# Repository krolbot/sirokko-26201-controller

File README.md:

# Sirokko 262.01

Контроллер отопителя Sirokko 262.01 на ESP32-S3. Управляет розжигом, муфтой топливного насоса и вентилятором, поддерживает температуру помещения. Управление — с TFT-панели с энкодером или из браузера по Wi-Fi.

[Скачать прошивку](https://github.com/krolbot/sirokko-26201-controller/releases/latest/download/Sirokko-firmware.zip) · [Руководство пользователя](docs/user-guide.md) · [Схема PDF](hardware/schematic.pdf)

## Возможности

- Розжиг, контроль температур и охлаждающая продувка после остановки.
- Ручное управление и поддержание температуры помещения, таймер отключения.
- Две термопары K через MAX31856 и комнатный датчик DS18B20.
- TFT 2,4″ с энкодером EC11 и кнопкой пуска/остановки; веб-интерфейс на русском языке.
- Подписанные обновления прошивки по Wi-Fi.

Питание — **24 В DC**. Вентилятор подключается через внешний регулятор **HC-160A S2**. Используется модуль **YD-ESP32-S3 N16R8 V1.4**.

Проект не испытывался на реальном оборудовании.

## Плата и компоненты

[Ведомость компонентов](hardware/BOM.md) содержит артикулы, количества, ссылки ChipDip и требования к внешним модулям. Есть [CSV](hardware/bom.csv) для закупки. Подключения, распиновки и порядок монтажа — в [инструкции сборки](docs/assembly.md).

Для заказа голой платы нужен [Gerber ZIP](manufacturing/pcb/gerbers.zip): **281 × 170 мм, 2 слоя, FR-4 1,6 мм, медь 35 мкм**. Для заказа монтажа — [BOM, координаты и сборочный чертёж](manufacturing/README.md).

## Прошивка

[Готовый USB-комплект](https://github.com/krolbot/sirokko-26201-controller/releases/latest/download/Sirokko-firmware.zip) включает загрузчик, таблицу разделов и приложение. [Руководство](docs/user-guide.md) описывает запись, первоначальную настройку и управление. Перед первым запуском задайте параметры отопителя по руководству.

Для сборки из исходников нужны ESP-IDF **5.2.3** и Node.js **26**. Команды сборки и подписи OTA — в [firmware/README.md](firmware/README.md).

## Файлы проекта

- [hardware/](hardware/) — проект KiCad 10, библиотеки, схема и компоненты.
- [firmware/](firmware/) — прошивка ESP32-S3 и веб-интерфейс.
- [manufacturing/](manufacturing/) — Gerber, сверловка, BOM и координаты для монтажа.
- [docs/](docs/) — сборка, подключение и руководство пользователя.

[Все файлы выпуска](https://github.com/krolbot/sirokko-26201-controller/releases/latest) · [Сообщить о проблеме](https://github.com/krolbot/sirokko-26201-controller/issues)

## Лицензии

Общая лицензия не назначена. Лицензии сторонних материалов: [KiCad](hardware/KICAD_LIBRARIES_LICENSE.md), [прошивка](firmware/third_party/README.md), [веб-интерфейс](firmware/web_ui/THIRD_PARTY_NOTICES.txt).

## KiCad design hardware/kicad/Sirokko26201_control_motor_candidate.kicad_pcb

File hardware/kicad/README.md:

> **Статус этапов:** проект платы, разводка и комплект изготовления завершены и приняты. Изготовление/сборка, реализация прошивки и физические испытания — следующие отдельные этапы. Отсутствие испытаний или готовой прошивки само по себе не блокирует изготовление голой PCB. Следующий совместный шаг — согласование функционала прошивки без изменения кода. [Подробнее / Stage definitions](../../docs/PROJECT_STAGES_RU.md).

# KiCad — действующий проект Sirokko

Открывайте `Sirokko26201_control_motor_candidate.kicad_pro` в KiCad 10.0.8. В комплекте одна основная PCB, пять листов схемы, библиотеки и проектные модели. Вместо собственной панели используется покупной TFT 2.4″ + EC11.

- PCB SHA256: `0ed3728e0cd427c01e9509a6aff25a2870087f775708396bfdd9fabb0b346e82`.
- Root SCH SHA256: `0b85bf2f4921b25a1c3126348eb176a88c7e3b29ca474c2d7229c4367e0a5cf5`.
- PRO SHA256: `11029d86464484cea63d73aa802bad95c1a6805aee11e841fc78322e9d2bc0d6`.
- Контур 281 × 170 мм; 73 посадки, 303 площадки, 663 сегмента, 115 переходов, 25 зон.
- DRC: 0 нарушений, 0 разрывов, без ignored checks. ERC: 0 зарегистрированных нарушений при четырёх сохранённых проектных ignored checks.
- Сверены 252 электрических назначения pin→net, 251 отверстие и 60 позиций установки. Сохранены UUID, сети и локальная геометрия всех 303 площадок; В v6 J32 и правый блок перекомпонованы; в v7 переразведены цепи и перенесены R7/R8 для свободного доступа к J29. 178 → 147 → 115 переходов; глобальный минимум не доказан.

**Окончательные управляющие выводы TFT:** RES = GPIO6/J1.6; DC = GPIO41/J3.7; CS = GPIO42/J3.6. Загрузочные GPIO3/46 не используются. GPIO9/10 остаются выборами MAX31856 и не заняты TFT. Старые описания назначения DC/CS на GPIO9/10 неверны.

J32 — IDC 2×6, SPI 3.3 В, кабель до 100 мм. Соединение с модулем не 1:1: [точная распиновка](../../docs/TFT24_INTERFACE_RU.md). [Текущие файлы изготовления и проверки](../../manufacturing/current/README_RU.md).

Неиспользуемые библиотечные символы не являются установленными компонентами. Стандартные и условные 3D-модели не доказывают полную геометрию сборки. `production_release=false`, `physical_tests=false`; KEY0 подключена аппаратно. Её программный обработчик не входит в этот выпуск; прошивка и локальный интерфейс требуют согласования.

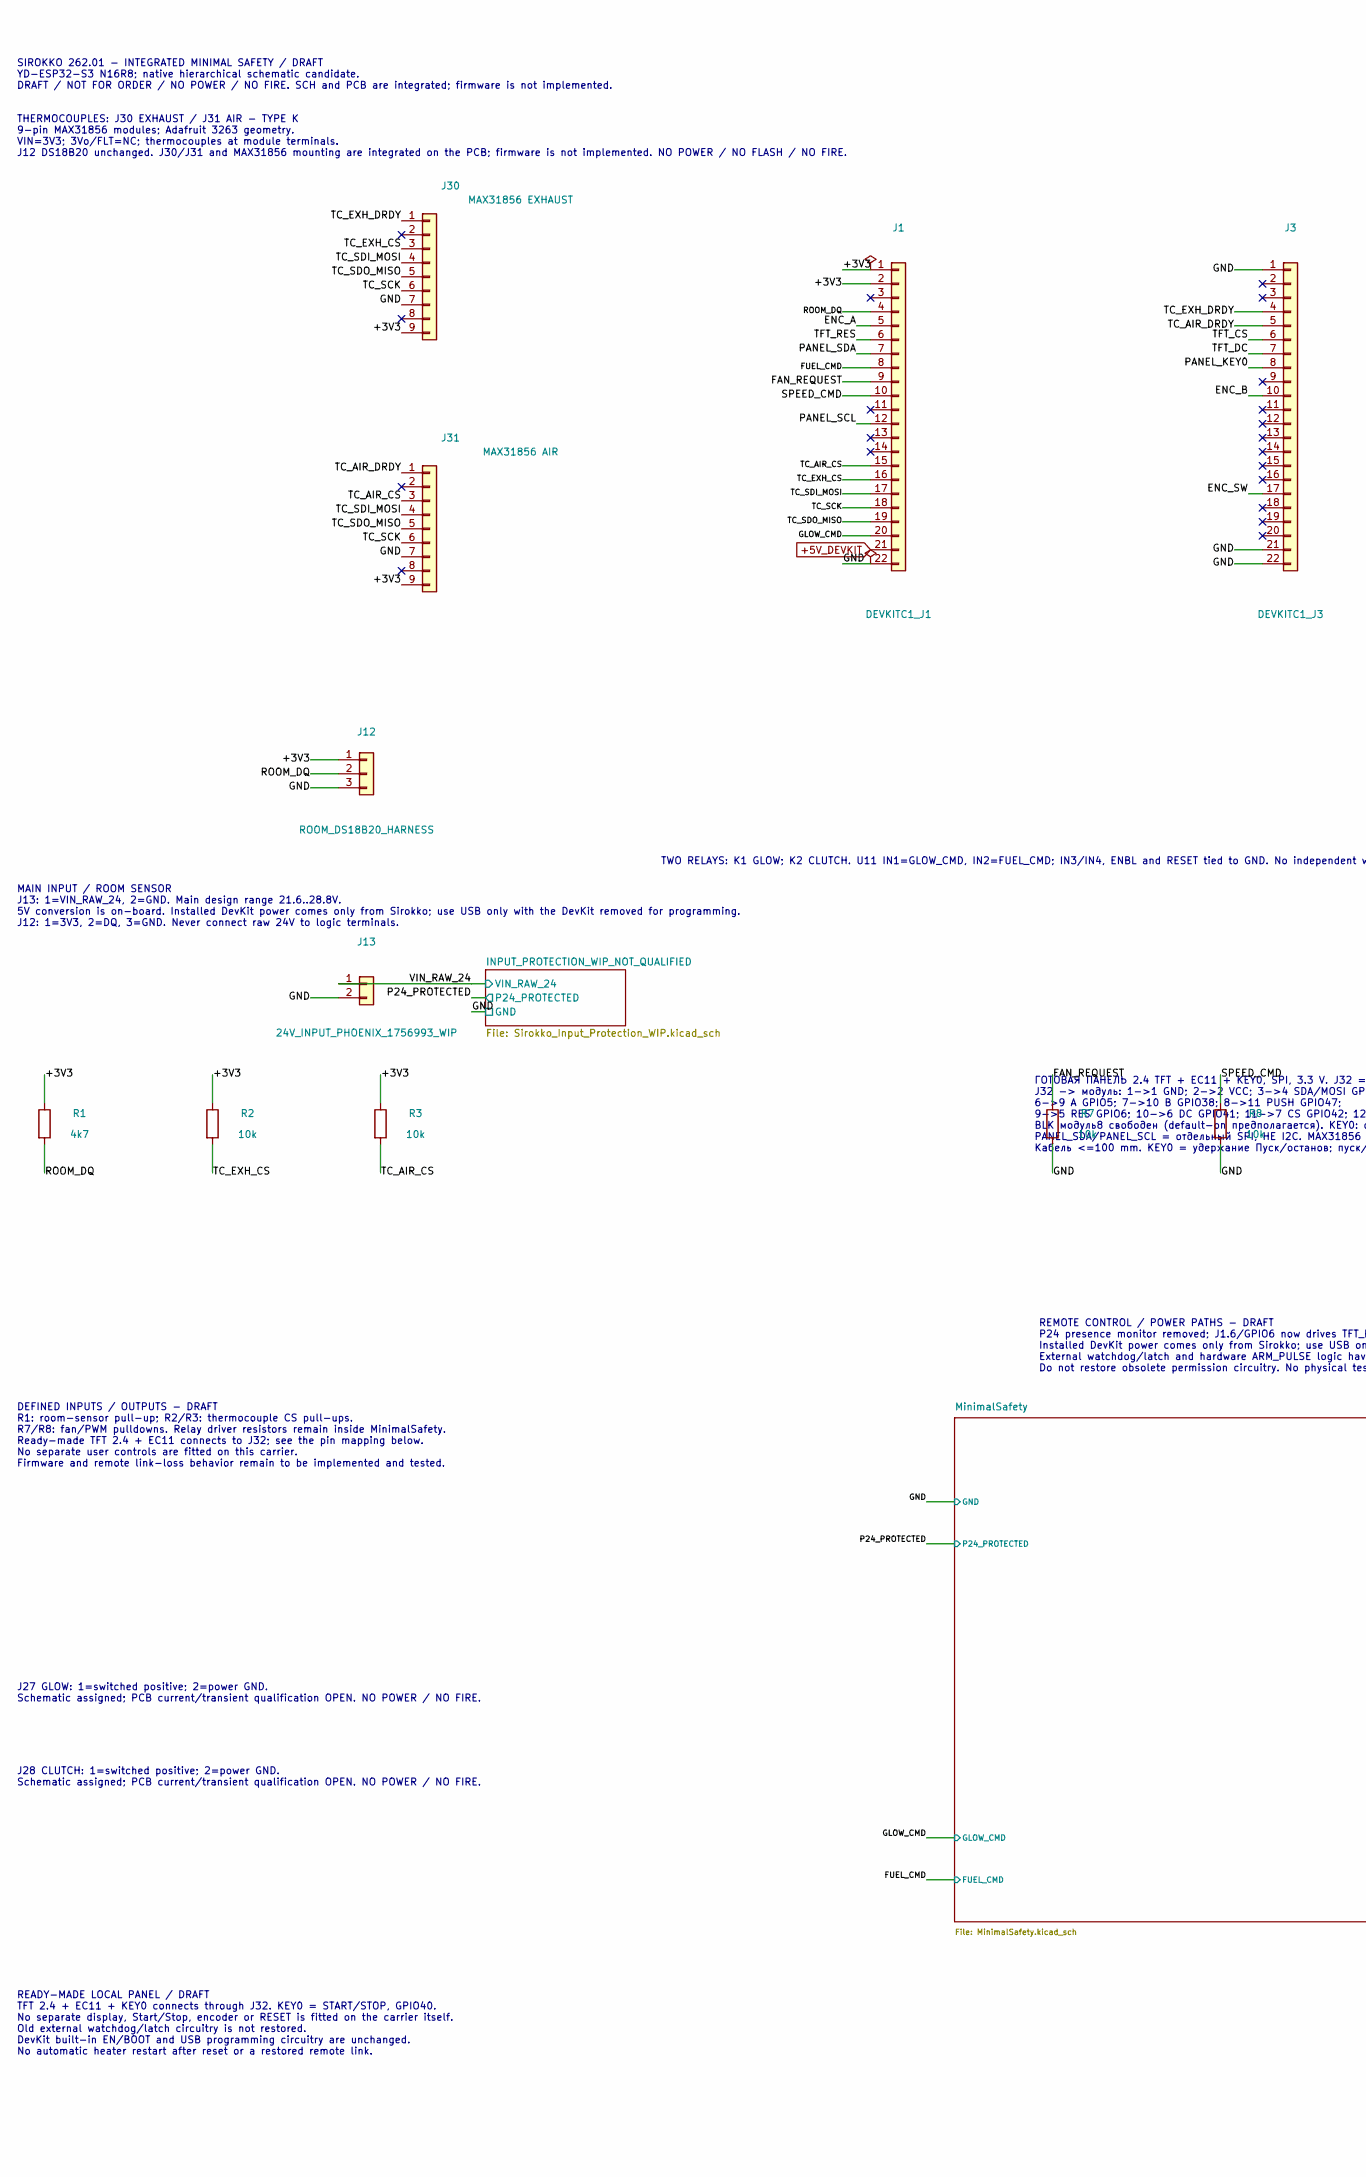
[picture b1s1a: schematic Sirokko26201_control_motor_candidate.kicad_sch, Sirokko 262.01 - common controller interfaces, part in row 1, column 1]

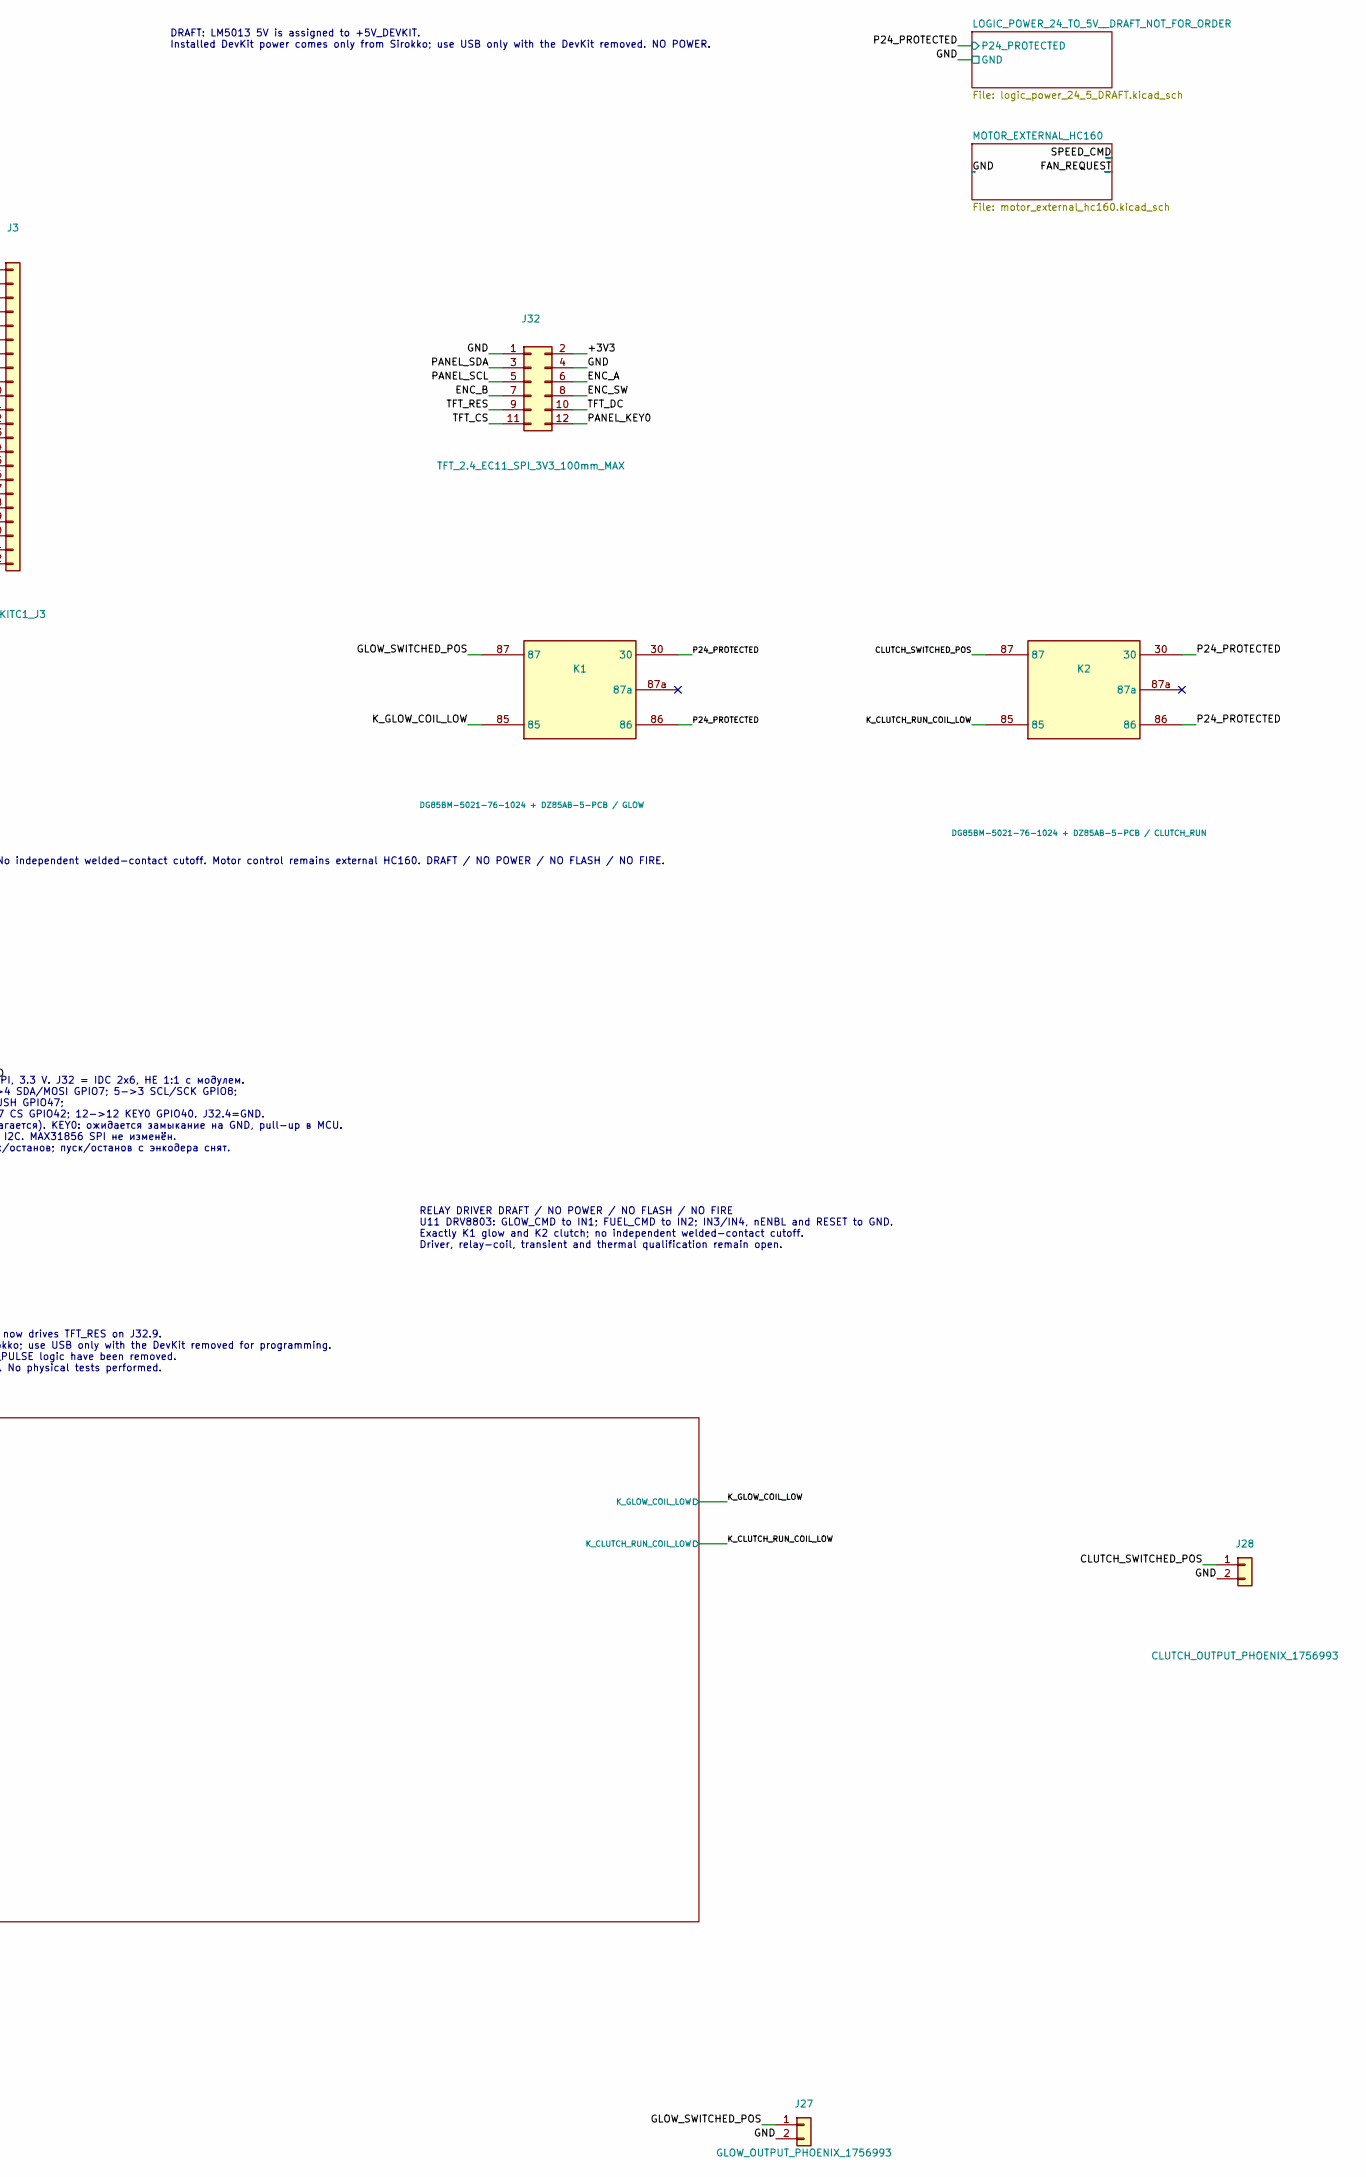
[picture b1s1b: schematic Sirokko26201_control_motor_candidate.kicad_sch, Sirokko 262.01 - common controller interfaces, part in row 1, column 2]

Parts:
J1: DEVKITC1_J1; PinSocket_1x22_P2.54mm_Vertical; MPN SSQ-122-01-T-S
J3: DEVKITC1_J3; PinSocket_1x22_P2.54mm_Vertical; MPN SSQ-122-01-T-S
J12: ROOM_DS18B20_HARNESS; TerminalBlock_Phoenix_MKDS-1,5-3-5.08_1x03_P5.08mm_Horizont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; MPN 1715734
J13: 24V_INPUT_PHOENIX_1756993_WIP; Phoenix_1756993_MKDS5HV_2_9.52_ZSZS_3D_ENVELOPE; MPN 1756993
J27: GLOW_OUTPUT_PHOENIX_1756993; Phoenix_1756993_MKDS5HV_2_9.52_ZSZS_3D_ENVELOPE; MPN 1756993
J28: CLUTCH_OUTPUT_PHOENIX_1756993; Phoenix_1756993_MKDS5HV_2_9.52_ZSZS_3D_ENVELOPE; MPN 1756993
J30: MAX31856 EXHAUST; Samtec_SSW-109-01-T-S_1x09_P2.54mm_D1.04mm; MPN SSW-109-01-T-S
J31: MAX31856 AIR; Samtec_SSW-109-01-T-S_1x09_P2.54mm_D1.04mm; MPN SSW-109-01-T-S
J32: TFT_2.4_EC11_SPI_3V3_100mm_MAX; IDC-Header_2x06_P2.54mm_Vertical
K1: DG85BM-5021-76-1024 + DZ85AB-5-PCB / GLOW; DZ85AB_5_PCB_DG85BM_ENVELOPE; MPN DG85BM-5021-76-1024 + DZ85AB-5-PCB
K2: DG85BM-5021-76-1024 + DZ85AB-5-PCB / CLUTCH_RUN; DZ85AB_5_PCB_DG85BM_ENVELOPE; MPN DG85BM-5021-76-1024 + DZ85AB-5-PCB
R1: 4k7; R_Axial_DIN0207_L6.3mm_D2.5mm_P10.16mm_Horizontal; MPN MFR-25FTE52-4K7
R2, R3, R7, R8: 10k; R_Axial_DIN0207_L6.3mm_D2.5mm_P10.16mm_Horizontal; MPN MFR-25FBF52-10K

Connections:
+5V_DEVKIT: J1.21; also elsewhere on the board
/+3V3: J1.1, J1.2, J12.1, J30.9, J31.9, J32.2, R1.1, R2.1, R3.1
/CLUTCH_SWITCHED_POS: J28.1, K2.87
/ENC_A: J1.5, J32.6
/ENC_B: J3.10, J32.7
/ENC_SW: J3.17, J32.8
/FAN_REQUEST: J1.9, R7.1; also elsewhere on the board
/FUEL_CMD: J1.8; also elsewhere on the board
/GLOW_CMD: J1.20; also elsewhere on the board
/GLOW_SWITCHED_POS: J27.1, K1.87
/GND: J1.22, J3.1, J3.21, J3.22, J12.3, J13.2, J27.2, J28.2, J30.7, J31.7, J32.1, J32.4, R7.2, R8.2; also elsewhere on the board
/K_CLUTCH_RUN_COIL_LOW: K2.85; also elsewhere on the board
/K_GLOW_COIL_LOW: K1.85; also elsewhere on the board
/P24_PROTECTED: K1.30, K1.86, K2.30, K2.86; also elsewhere on the board
/PANEL_KEY0: J3.8, J32.12
/PANEL_SCL: J1.12, J32.5
/PANEL_SDA: J1.7, J32.3
/ROOM_DQ: J1.4, J12.2, R1.2
/SPEED_CMD: J1.10, R8.1; also elsewhere on the board
/TC_AIR_CS: J1.15, J31.3, R3.2
/TC_AIR_DRDY: J3.5, J31.1
/TC_EXH_CS: J1.16, J30.3, R2.2
/TC_EXH_DRDY: J3.4, J30.1
/TC_SCK: J1.18, J30.6, J31.6
/TC_SDI_MOSI: J1.17, J30.4, J31.4
/TC_SDO_MISO: J1.19, J30.5, J31.5
/TFT_CS: J3.6, J32.11
/TFT_DC: J3.7, J32.10
/TFT_RES: J1.6, J32.9
/VIN_RAW_24: J13.1; also elsewhere on the board

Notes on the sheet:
SIROKKO 262.01 - INTEGRATED MINIMAL SAFETY / DRAFT YD-ESP32-S3 N16R8; native hierarchical schematic candidate. DRAFT / NOT FOR ORDER / NO POWER / NO FIRE. SCH and PCB are integrated; firmware is not implemented.
THERMOCOUPLES: J30 EXHAUST / J31 AIR - TYPE K 9-pin MAX31856 modules; Adafruit 3263 geometry. VIN=3V3; 3Vo/FLT=NC; thermocouples at module terminals. J12 DS18B20 unchanged. J30/J31 and MAX31856 mounting are integrated on the PCB; firmware is not implemented. NO POWER / NO FLASH / NO FIRE.
TWO RELAYS: K1 GLOW; K2 CLUTCH. U11 IN1=GLOW_CMD, IN2=FUEL_CMD; IN3/IN4, ENBL and RESET tied to GND. No independent welded-contact cutoff. Motor control remains external HC160. DRAFT / NO POWER / NO FLASH / NO FIRE.
MAIN INPUT / ROOM SENSOR J13: 1=VIN_RAW_24, 2=GND. Main design range 21.6..28.8V. 5V conversion is on-board. Installed DevKit power comes only from Sirokko; use USB only with the DevKit removed for programming. J12: 1=3V3, 2=DQ, 3=GND. Never connect raw 24V to logic terminals.
DEFINED INPUTS / OUTPUTS - DRAFT R1: room-sensor pull-up; R2/R3: thermocouple CS pull-ups. R7/R8: fan/PWM pulldowns. Relay driver resistors remain inside MinimalSafety. Ready-made TFT 2.4 + EC11 connects to J32; see the pin mapping below. No separate user controls are fitted on this carrier. Firmwa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
REMOTE CONTROL / POWER PATHS - DRAFT P24 presence monitor removed; J1.6/GPIO6 now drives TFT_RES on J32.9. Installed DevKit power comes only from Sirokko; use USB only with the DevKit removed for programming. External watchdog/latch and hardware ARM_PULSE logic have been removed. Do not restore obs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
DRAFT: LM5013 5V is assigned to +5V_DEVKIT. Installed DevKit power comes only from Sirokko; use USB only with the DevKit removed. NO POWER.
J27 GLOW: 1=switched positive; 2=power GND. Schematic assigned; PCB current/transient qualification OPEN. NO POWER / NO FIRE.
J28 CLUTCH: 1=switched positive; 2=power GND. Schematic assigned; PCB current/transient qualification OPEN. NO POWER / NO FIRE.
RELAY DRIVER DRAFT / NO POWER / NO FLASH / NO FIRE U11 DRV8803: GLOW_CMD to IN1; FUEL_CMD to IN2; IN3/IN4, nENBL and RESET to GND. Exactly K1 glow and K2 clutch; no independent welded-contact cutoff. Driver, relay-coil, transient and thermal qualification remain open.
READY-MADE LOCAL PANEL / DRAFT TFT 2.4 + EC11 + KEY0 connects through J32. KEY0 = START/STOP, GPIO40. No separate display, Start/Stop, encoder or RESET is fitted on the carrier itself. Old external watchdog/latch circuitry is not restored. DevKit built-in EN/BOOT and USB programming circuitry are u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
ГОТОВАЯ ПАНЕЛЬ 2.4 TFT + EC11 + KEY0, SPI, 3.3 V. J32 = IDC 2x6, НЕ 1:1 с модулем. J32 -> модуль: 1->1 GND; 2->2 VCC; 3->4 SDA/MOSI GPIO7; 5->3 SCL/SCK GPIO8; 6->9 A GPIO5; 7->10 B GPIO38; 8->11 PUSH GPIO47; 9->5 RES GPIO6; 10->6 DC GPIO41; 11->7 CS GPIO42; 12->12 KEY0 GPIO40. J32.4=GND. BLK модуль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

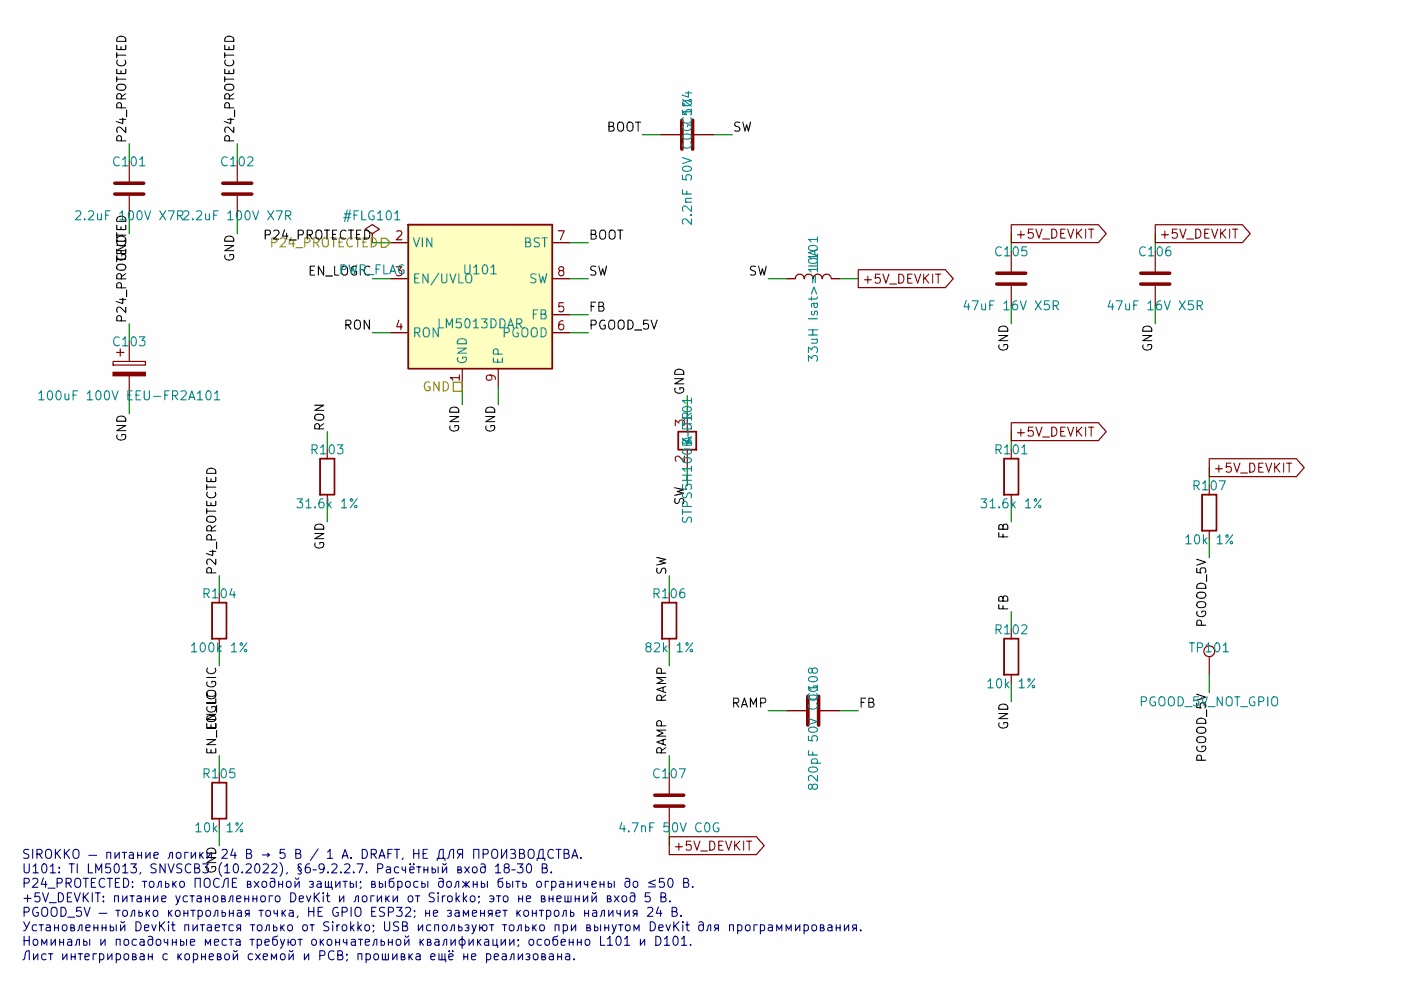
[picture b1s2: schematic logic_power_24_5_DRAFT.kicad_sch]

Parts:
C101, C102: 2.2uF 100V X7R; C_1210_3225Metric; MPN GRM32ER72A225KA35L
C103: 100uF 100V EEU-FR2A101; CP_Radial_D10.0mm_P5.00mm_Courtyard_D11.0mm; MPN EEU-FR2A101
C104: 2.2nF 50V C0G 5%; C_0603_1608Metric; MPN GRM1885C1H222JA01D
C105, C106: 47uF 16V X5R; C_1210_3225Metric; MPN GRM32ER61C476KE15L
C107: 4.7nF 50V C0G; C_0603_1608Metric; MPN GRM1885C1H472JA01D
C108: 820pF 50V C0G; C_0603_1608Metric; MPN CC0603JRNPO9BN821
D101: STPS5H100B-TR; TO-252-2; MPN STPS5H100B-TR
L101: 33uH Isat>=10A; L_Bourns_SRP1770TA_16.9x16.9mm; MPN SRP1770TA-330M
R101, R103: 31.6k 1%; R_0603_1608Metric; MPN RC0603FR-0731K6L
R102, R105, R107: 10k 1%; R_0603_1608Metric; MPN RC0603FR-0710KL
R104: 100k 1%; R_0603_1608Metric; MPN RC0603FR-07100KL
R106: 82k 1%; R_0603_1608Metric; MPN RC0603FR-0782KL
TP101: PGOOD_5V_NOT_GPIO; TestPoint_Keystone_5015_Micro_Mini; MPN 5015
U101: LM5013DDAR; DDA0008B_LM5013DDAR_TI4214849B_3D; MPN LM5013DDAR

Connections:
+5V_DEVKIT: C105.1, C106.1, C107.2, L101.2, R101.1, R107.1; also elsewhere on the board
/GND: C101.2, C102.2, C103.2, C105.2, C106.2, D101.3 (A), R102.2, R103.2, R105.2, U101.1 (GND), U101.9 (EP); also elsewhere on the board
/LOGIC_POWER_24_TO_5V__DRAFT_NOT_FOR_ORDER/BOOT: C104.1, U101.7 (BST)
/LOGIC_POWER_24_TO_5V__DRAFT_NOT_FOR_ORDER/EN_LOGIC: R104.2, R105.1, U101.3 (EN/UVLO)
/LOGIC_POWER_24_TO_5V__DRAFT_NOT_FOR_ORDER/FB: C108.2, R101.2, R102.1, U101.5 (FB)
/LOGIC_POWER_24_TO_5V__DRAFT_NOT_FOR_ORDER/PGOOD_5V: R107.2, TP101.1, U101.6 (PGOOD)
/LOGIC_POWER_24_TO_5V__DRAFT_NOT_FOR_ORDER/RAMP: C107.1, C108.1, R106.2
/LOGIC_POWER_24_TO_5V__DRAFT_NOT_FOR_ORDER/RON: R103.1, U101.4 (RON)
/LOGIC_POWER_24_TO_5V__DRAFT_NOT_FOR_ORDER/SW: C104.2, D101.2 (K), L101.1, R106.1, U101.8 (SW)
/P24_PROTECTED: C101.1, C102.1, C103.1, R104.1, U101.2 (VIN); also elsewhere on the board

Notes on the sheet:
SIROKKO — питание логики 24 В → 5 В / 1 А. DRAFT, НЕ ДЛЯ ПРОИЗВОДСТВА. U101: TI LM5013, SNVSCB3 (10.2022), §6–9.2.2.7. Расчётный вход 18–30 В. P24_PROTECTED: только ПОСЛЕ входной защиты; выбросы должны быть ограничены до ≤50 В. +5V_DEVKIT: питание установленного DevKit и логики от Sirokko; это не в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

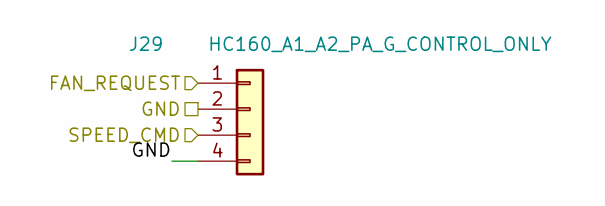
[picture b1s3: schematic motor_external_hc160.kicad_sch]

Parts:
J29: HC160_A1_A2_PA_G_CONTROL_ONLY; TerminalBlock_Phoenix_MKDS-1,5-4-5.08_1x04_P5.08mm_Horizont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; MPN 1715747

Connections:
/FAN_REQUEST: J29.1; also elsewhere on the board
/GND: J29.2, J29.4; also elsewhere on the board
/SPEED_CMD: J29.3; also elsewhere on the board

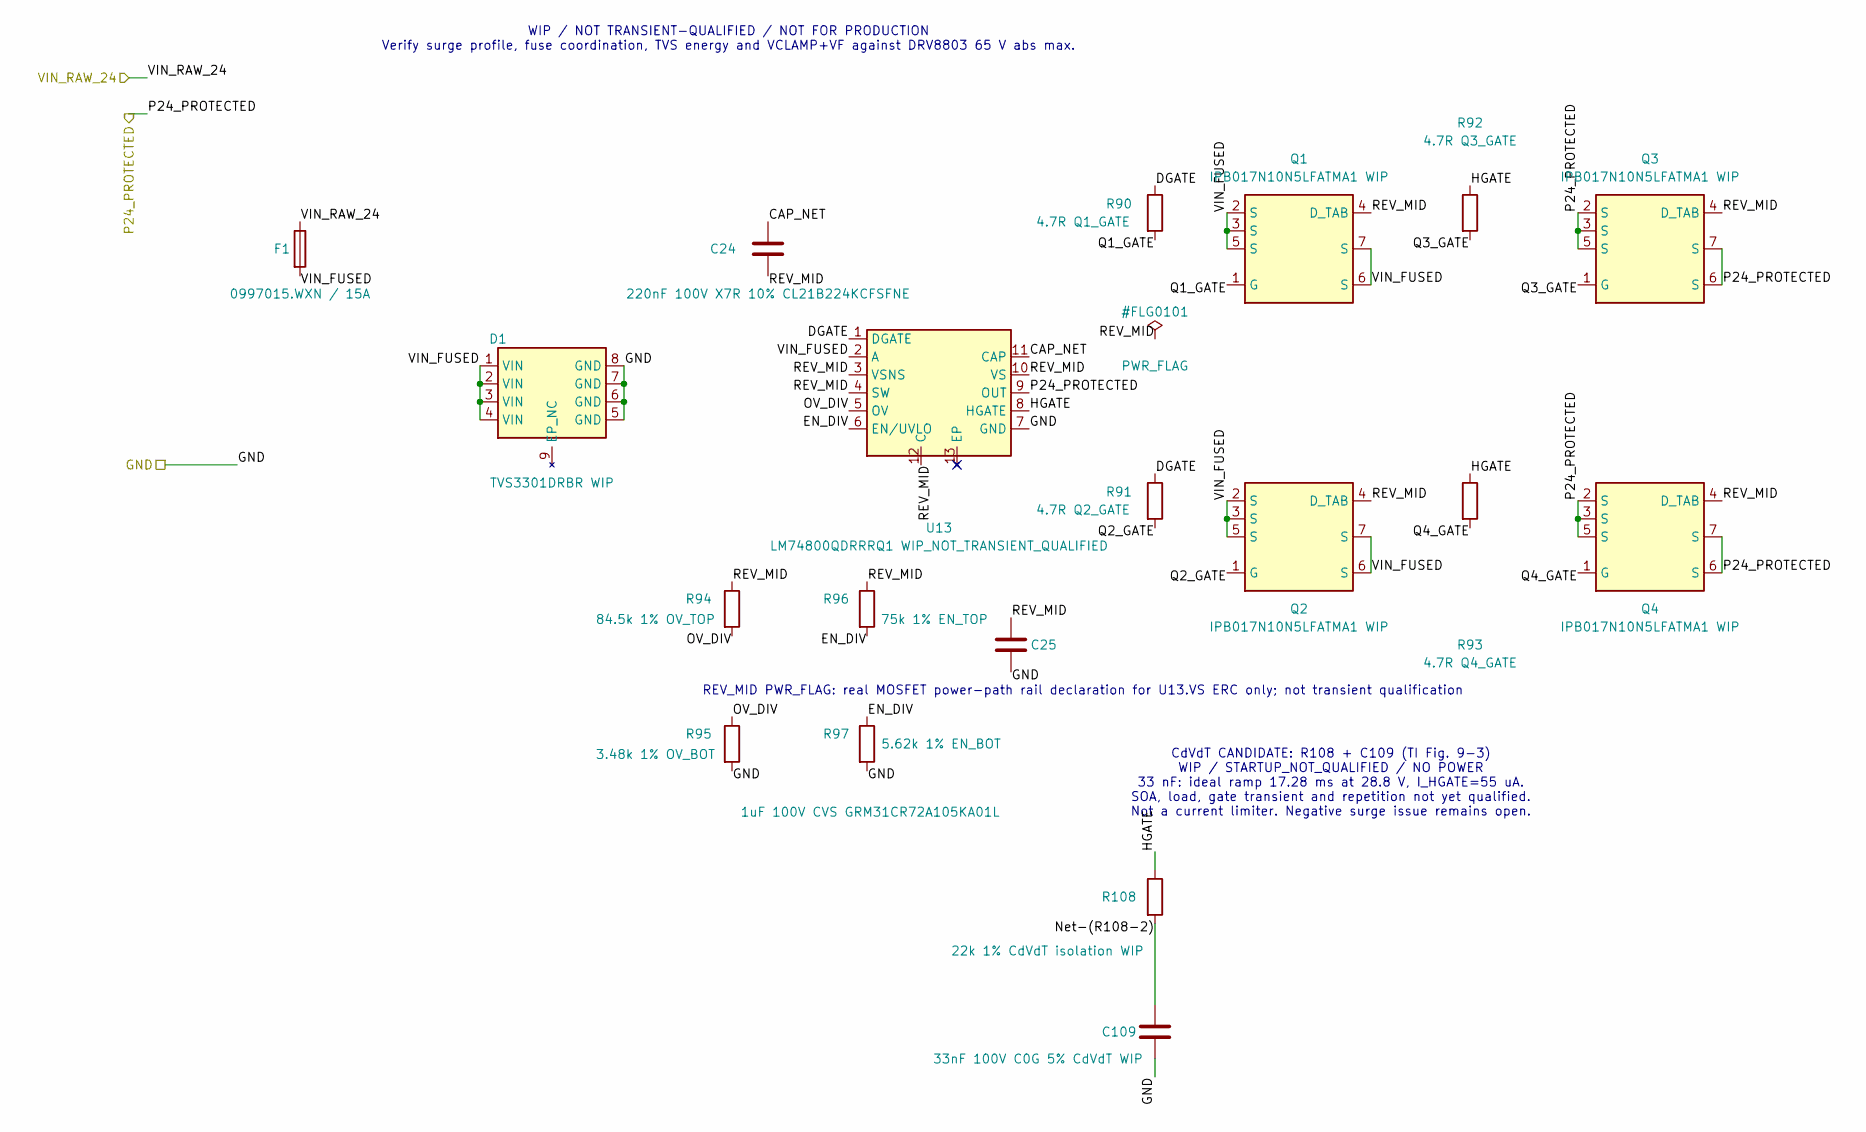
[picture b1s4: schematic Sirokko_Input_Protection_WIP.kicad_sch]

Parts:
C24: 220nF 100V X7R 10% CL21B224KCFSFNE; C_0805_2012Metric; MPN CL21B224KCFSFNE
C25: 1uF 100V CVS GRM31CR72A105KA01L; GRM31_1206_Murata_Reflow; MPN GRM31CR72A105KA01L
C109: 33nF 100V C0G 5% CdVdT WIP; C_0805_2012Metric; MPN GRM2195C2A333JE01J
D1: TVS3301DRBR WIP; VSON-8-1EP_3x3mm_P0.65mm_EP1.65x2.4mm; MPN TVS3301DRBR
F1: 0997015.WXN / 15A; Keystone_3568_MINI_Blade_3D_ENVELOPE; MPN 0997015.WXN + 3568
Q1, Q2, Q3, Q4: IPB017N10N5LFATMA1 WIP; Infineon_PG_TO263_7_IPB017N10N5LF; MPN IPB017N10N5LFATMA1
R90: 4.7R Q1_GATE; R_0805_2012Metric; MPN RC0805FR-074R7L
R91: 4.7R Q2_GATE; R_0805_2012Metric; MPN RC0805FR-074R7L
R92: 4.7R Q3_GATE; R_0805_2012Metric; MPN RC0805FR-074R7L
R93: 4.7R Q4_GATE; R_0805_2012Metric; MPN RC0805FR-074R7L
R94: 84.5k 1% OV_TOP; R_0805_2012Metric; MPN RC0805FR-0784K5L
R95: 3.48k 1% OV_BOT; R_0805_2012Metric; MPN RC0805FR-073K48L
R96: 75k 1% EN_TOP; R_0805_2012Metric; MPN RC0805FR-0775KL
R97: 5.62k 1% EN_BOT; R_0805_2012Metric; MPN RC0805FR-075K62L
R108: 22k 1% CdVdT isolation WIP; R_1210_3225Metric; MPN RC1210FR-0722KL
U13: LM74800QDRRRQ1 WIP_NOT_TRANSIENT_QUALIFIED; WSON-12-1EP_3x3mm_P0.5mm_EP1.5x2.5mm; MPN LM74800QDRRRQ1

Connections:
/GND: C25.2, C109.2, D1.5 (GND), D1.6 (GND), D1.7 (GND), D1.8 (GND), R95.2, R97.2, U13.7 (GND); also elsewhere on the board
/INPUT_PROTECTION_WIP_NOT_QUALIFIED/CAP_NET: C24.1, U13.11 (CAP)
/INPUT_PROTECTION_WIP_NOT_QUALIFIED/DGATE: R90.1, R91.1, U13.1 (DGATE)
/INPUT_PROTECTION_WIP_NOT_QUALIFIED/EN_DIV: R96.2, R97.1, U13.6 (EN/UVLO)
/INPUT_PROTECTION_WIP_NOT_QUALIFIED/HGATE: R92.1, R93.1, R108.1, U13.8 (HGATE)
/INPUT_PROTECTION_WIP_NOT_QUALIFIED/Net-(R108-2): C109.1, R108.2
/INPUT_PROTECTION_WIP_NOT_QUALIFIED/OV_DIV: R94.2, R95.1, U13.5 (OV)
/INPUT_PROTECTION_WIP_NOT_QUALIFIED/Q1_GATE: Q1.1 (G), R90.2
/INPUT_PROTECTION_WIP_NOT_QUALIFIED/Q2_GATE: Q2.1 (G), R91.2
/INPUT_PROTECTION_WIP_NOT_QUALIFIED/Q3_GATE: Q3.1 (G), R92.2
/INPUT_PROTECTION_WIP_NOT_QUALIFIED/Q4_GATE: Q4.1 (G), R93.2
/INPUT_PROTECTION_WIP_NOT_QUALIFIED/REV_MID: C24.2, C25.1, Q1.4 (D_TAB), Q2.4 (D_TAB), Q3.4 (D_TAB), Q4.4 (D_TAB), R94.1, R96.1, U13.3 (VSNS), U13.4 (SW), U13.10 (VS), U13.12 (C)
/INPUT_PROTECTION_WIP_NOT_QUALIFIED/VIN_FUSED: D1.1 (VIN), D1.2 (VIN), D1.3 (VIN), D1.4 (VIN), F1.2, Q1.2 (S), Q1.3 (S), Q1.5 (S), Q1.6 (S), Q1.7 (S), Q2.2 (S), Q2.3 (S), Q2.5 (S), Q2.6 (S), Q2.7 (S), U13.2 (A)
/P24_PROTECTED: Q3.2 (S), Q3.3 (S), Q3.5 (S), Q3.6 (S), Q3.7 (S), Q4.2 (S), Q4.3 (S), Q4.5 (S), Q4.6 (S), Q4.7 (S), U13.9 (OUT); also elsewhere on the board
/VIN_RAW_24: F1.1; also elsewhere on the board

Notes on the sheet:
REV_MID PWR_FLAG: real MOSFET power-path rail declaration for U13.VS ERC only; not transient qualification
CdVdT CANDIDATE: R108 + C109 (TI Fig. 9-3) WIP / STARTUP_NOT_QUALIFIED / NO POWER 33 nF: ideal ramp 17.28 ms at 28.8 V, I_HGATE=55 uA. SOA, load, gate transient and repetition not yet qualified. Not a current limiter. Negative surge issue remains open.
WIP / NOT TRANSIENT-QUALIFIED / NOT FOR PRODUCTION Verify surge profile, fuse coordination, TVS energy and VCLAMP+VF against DRV8803 65 V abs max.

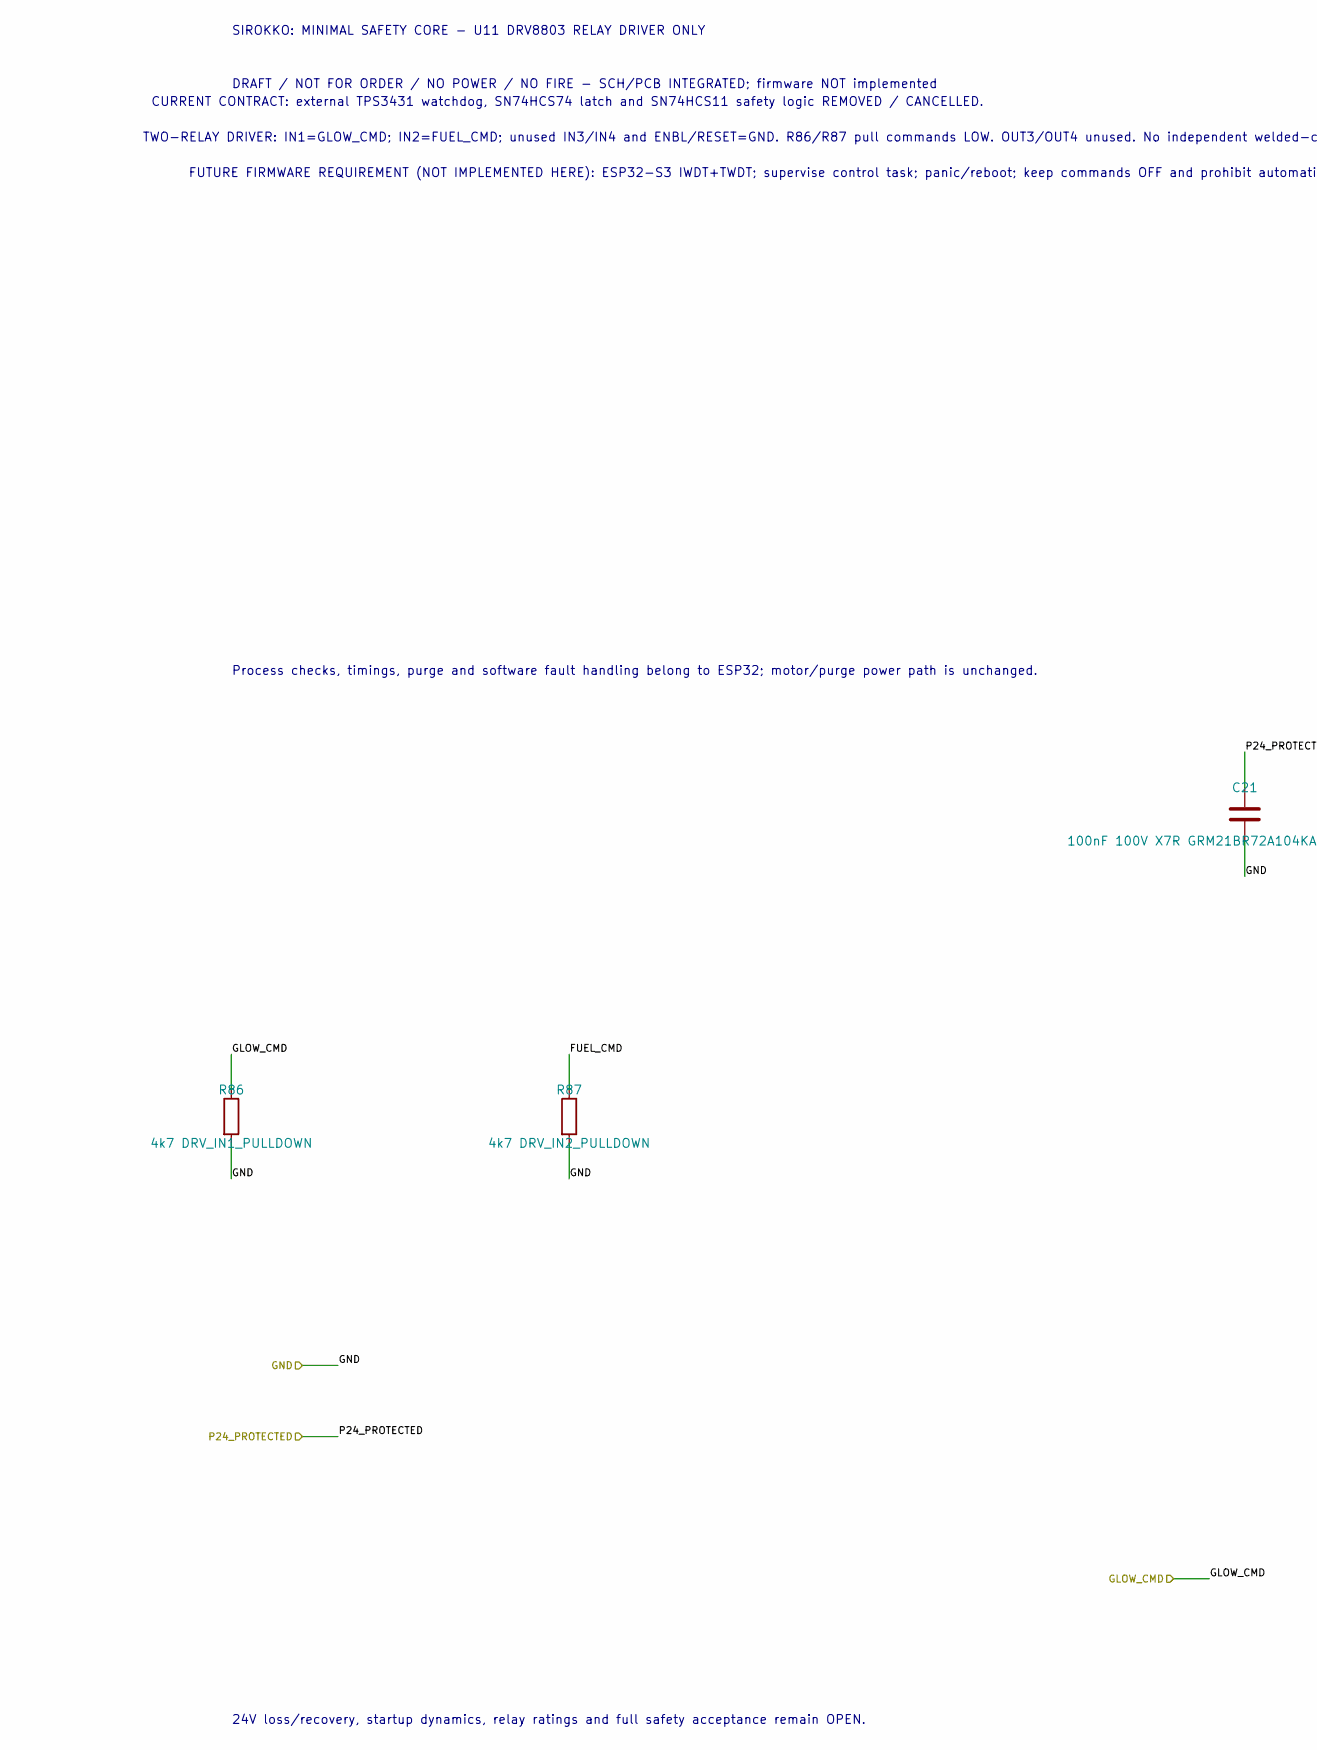
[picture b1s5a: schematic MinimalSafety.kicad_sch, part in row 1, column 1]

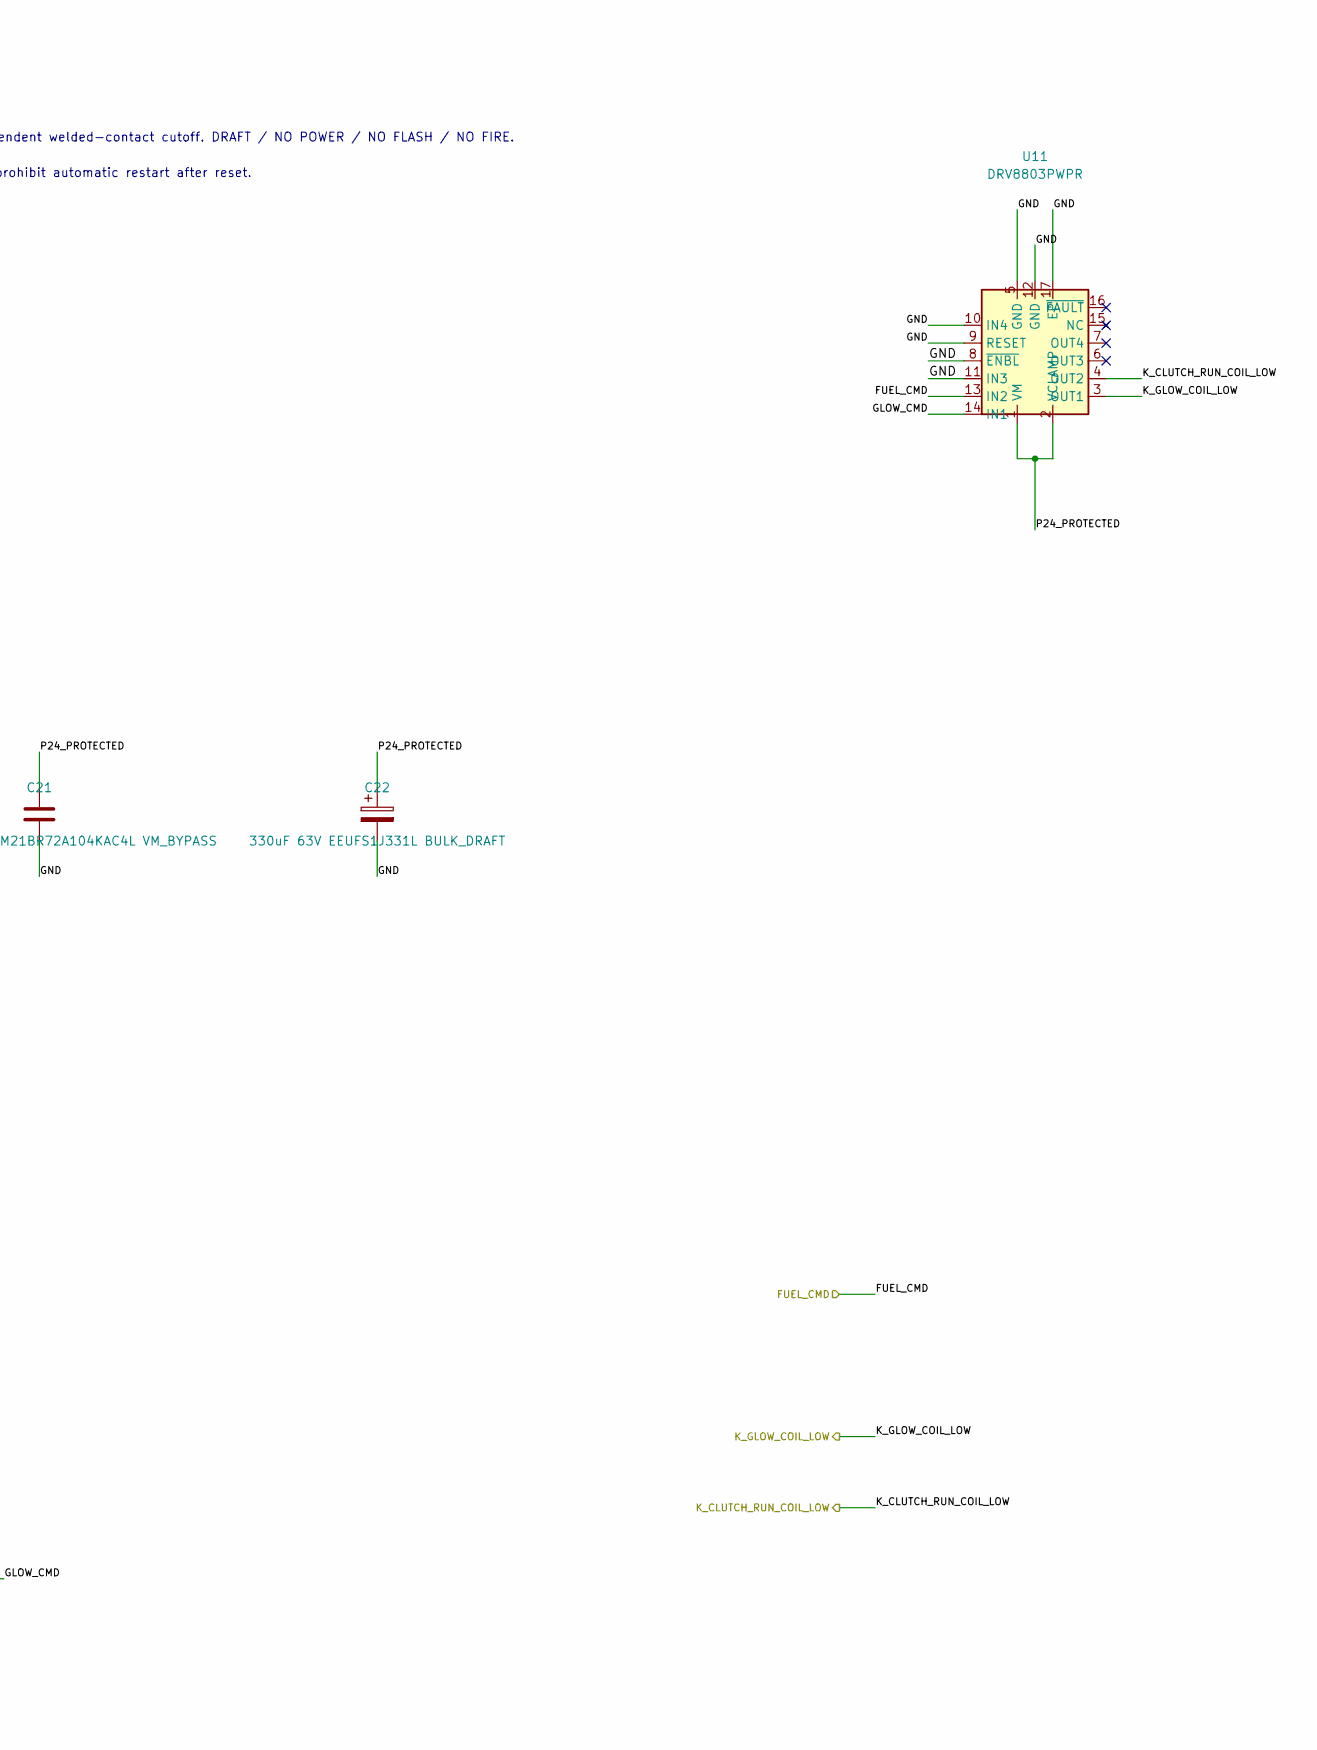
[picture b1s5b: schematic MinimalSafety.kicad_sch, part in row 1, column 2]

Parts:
C21: 100nF 100V X7R GRM21BR72A104KAC4L VM_BYPASS; C_0805_2012Metric; MPN GRM21BR72A104KAC4L
C22: 330uF 63V EEUFS1J331L BULK_DRAFT; CP_Radial_D10.0mm_P5.00mm; MPN EEUFS1J331L
R86: 4k7 DRV_IN1_PULLDOWN; R_Axial_DIN0207_L6.3mm_D2.5mm_P10.16mm_Horizontal; MPN MFR-25FTE52-4K7
R87: 4k7 DRV_IN2_PULLDOWN; R_Axial_DIN0207_L6.3mm_D2.5mm_P10.16mm_Horizontal; MPN MFR-25FTE52-4K7
U11: DRV8803PWPR; HTSSOP-16-1EP_4.4x5mm_P0.65mm_EP3x3mm; MPN DRV8803PWPR

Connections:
/FUEL_CMD: R87.1, U11.13 (IN2); also elsewhere on the board
/GLOW_CMD: R86.1, U11.14 (IN1); also elsewhere on the board
/GND: C21.2, C22.2, R86.2, R87.2, U11.5 (GND), U11.8 (~ENBL), U11.9 (RESET), U11.10 (IN4), U11.11 (IN3), U11.12 (GND), U11.17 (EP); also elsewhere on the board
/K_CLUTCH_RUN_COIL_LOW: U11.4 (OUT2); also elsewhere on the board
/K_GLOW_COIL_LOW: U11.3 (OUT1); also elsewhere on the board
/P24_PROTECTED: C21.1, C22.1, U11.1 (VM), U11.2 (VCLAMP); also elsewhere on the board

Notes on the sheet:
24V loss/recovery, startup dynamics, relay ratings and full safety acceptance remain OPEN.
Process checks, timings, purge and software fault handling belong to ESP32; motor/purge power path is unchanged.
DRAFT / NOT FOR ORDER / NO POWER / NO FIRE - SCH/PCB INTEGRATED; firmware NOT implemented
TWO-RELAY DRIVER: IN1=GLOW_CMD; IN2=FUEL_CMD; unused IN3/IN4 and ENBL/RESET=GND. R86/R87 pull commands LOW. OUT3/OUT4 unused. No independent welded-contact cutoff. DRAFT / NO POWER / NO FLASH / NO FIRE.
CURRENT CONTRACT: external TPS3431 watchdog, SN74HCS74 latch and SN74HCS11 safety logic REMOVED / CANCELLED.
FUTURE FIRMWARE REQUIREMENT (NOT IMPLEMENTED HERE): ESP32-S3 IWDT+TWDT; supervise control task; panic/reboot; keep commands OFF and prohibit automatic restart after reset.
SIROKKO: MINIMAL SAFETY CORE - U11 DRV8803 RELAY DRIVER ONLY
